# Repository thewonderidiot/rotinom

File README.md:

# rotinom
PCB and FPGA projects for an AGC test connector electrical simulation board, for testing the AGC Monitor.

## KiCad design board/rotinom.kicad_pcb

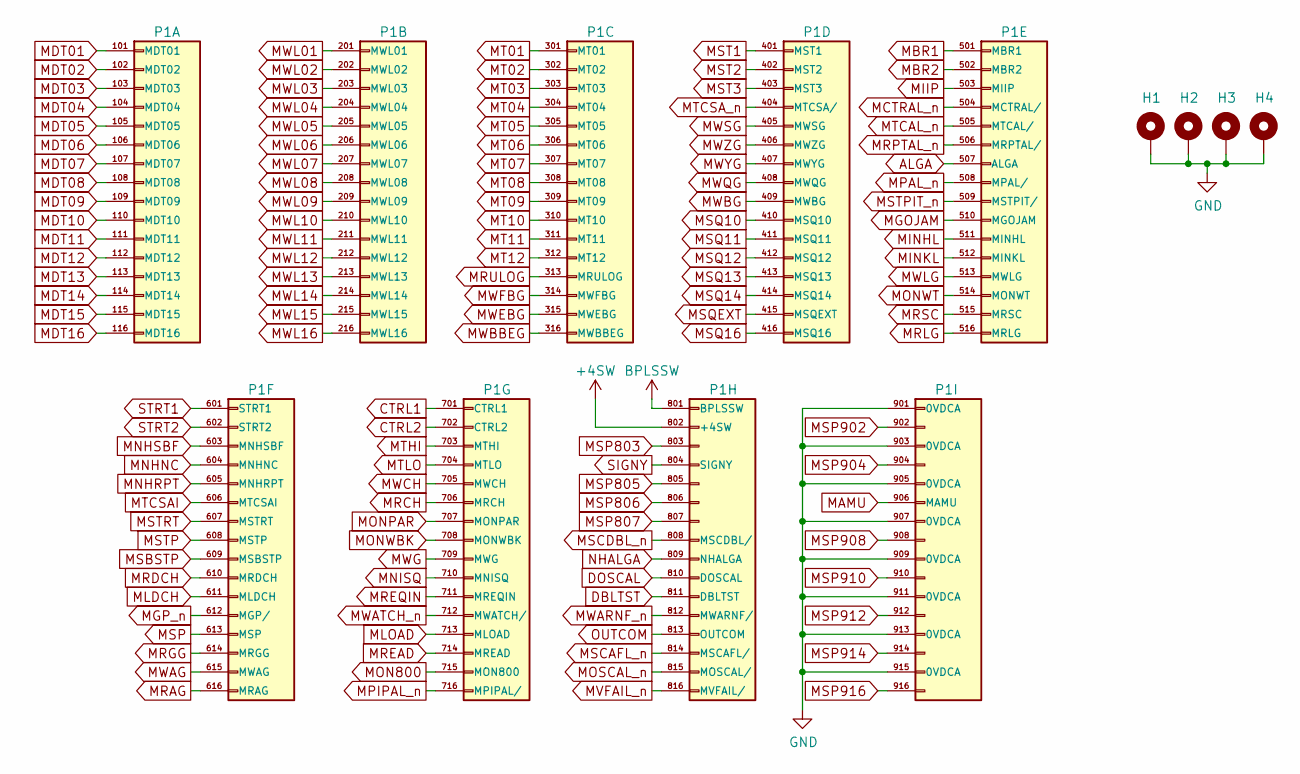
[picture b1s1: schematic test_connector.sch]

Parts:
H1, H2, H3, H4: MountingHole_Pad; MountingHole_ANSI_4
P1: test_connector

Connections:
+4SW: P1.802 (+4SW); also elsewhere on the board
ALGA: P1.507 (ALGA); also elsewhere on the board
BPLSSW: P1.801 (BPLSSW); also elsewhere on the board
CTRL1: P1.701 (CTRL1); also elsewhere on the board
CTRL2: P1.702 (CTRL2); also elsewhere on the board
DBLTST: P1.811 (DBLTST); also elsewhere on the board
DOSCAL: P1.810 (DOSCAL); also elsewhere on the board
GND: H1.1, H2.1, H3.1, H4.1, P1.901 (0VDCA), P1.903 (0VDCA), P1.905 (0VDCA), P1.907 (0VDCA), P1.909 (0VDCA), P1.911 (0VDCA), P1.913 (0VDCA), P1.915 (0VDCA); also elsewhere on the board
MAMU: P1.906 (MAMU); also elsewhere on the board
MBR1: P1.501 (MBR1); also elsewhere on the board
MBR2: P1.502 (MBR2); also elsewhere on the board
MCTRAL_n: P1.504 (MCTRAL/); also elsewhere on the board
MDT01: P1.101 (MDT01); also elsewhere on the board
MDT02: P1.102 (MDT02); also elsewhere on the board
MDT03: P1.103 (MDT03); also elsewhere on the board
MDT04: P1.104 (MDT04); also elsewhere on the board
MDT05: P1.105 (MDT05); also elsewhere on the board
MDT06: P1.106 (MDT06); also elsewhere on the board
MDT07: P1.107 (MDT07); also elsewhere on the board
MDT08: P1.108 (MDT08); also elsewhere on the board
MDT09: P1.109 (MDT09); also elsewhere on the board
MDT10: P1.110 (MDT10); also elsewhere on the board
MDT11: P1.111 (MDT11); also elsewhere on the board
MDT12: P1.112 (MDT12); also elsewhere on the board
MDT13: P1.113 (MDT13); also elsewhere on the board
MDT14: P1.114 (MDT14); also elsewhere on the board
MDT15: P1.115 (MDT15); also elsewhere on the board
MDT16: P1.116 (MDT16); also elsewhere on the board
MGOJAM: P1.510 (MGOJAM); also elsewhere on the board
MGP_n: P1.612 (MGP/); also elsewhere on the board
MIIP: P1.503 (MIIP); also elsewhere on the board
MINHL: P1.511 (MINHL); also elsewhere on the board
MINKL: P1.512 (MINKL); also elsewhere on the board
MLDCH: P1.611 (MLDCH); also elsewhere on the board
MLOAD: P1.713 (MLOAD); also elsewhere on the board
MNHNC: P1.604 (MNHNC); also elsewhere on the board
MNHRPT: P1.605 (MNHRPT); also elsewhere on the board
MNHSBF: P1.603 (MNHSBF); also elsewhere on the board
MNISQ: P1.710 (MNISQ); also elsewhere on the board
MON800: P1.715 (MON800); also elsewhere on the board
MONPAR: P1.707 (MONPAR); also elsewhere on the board
MONWBK: P1.708 (MONWBK); also elsewhere on the board
MONWT: P1.514 (MONWT); also elsewhere on the board
MOSCAL_n: P1.815 (MOSCAL/); also elsewhere on the board
MPAL_n: P1.508 (MPAL/); also elsewhere on the board
MPIPAL_n: P1.716 (MPIPAL/); also elsewhere on the board
MRAG: P1.616 (MRAG); also elsewhere on the board
MRCH: P1.706 (MRCH); also elsewhere on the board
MRDCH: P1.610 (MRDCH); also elsewhere on the board
MREAD: P1.714 (MREAD); also elsewhere on the board
MREQIN: P1.711 (MREQIN); also elsewhere on the board
MRGG: P1.614 (MRGG); also elsewhere on the board
MRLG: P1.516 (MRLG); also elsewhere on the board
MRPTAL_n: P1.506 (MRPTAL/); also elsewhere on the board
MRSC: P1.515 (MRSC); also elsewhere on the board
MRULOG: P1.313 (MRULOG); also elsewhere on the board
MSBSTP: P1.609 (MSBSTP); also elsewhere on the board
MSCAFL_n: P1.814 (MSCAFL/); also elsewhere on the board
MSCDBL_n: P1.808 (MSCDBL/); also elsewhere on the board
MSP: P1.613 (MSP); also elsewhere on the board
MSP803: P1.803; also elsewhere on the board
MSP805: P1.805; also elsewhere on the board
MSP806: P1.806; also elsewhere on the board
MSP807: P1.807; also elsewhere on the board
MSP902: P1.902; also elsewhere on the board
MSP904: P1.904; also elsewhere on the board
MSP908: P1.908; also elsewhere on the board
MSP910: P1.910; also elsewhere on the board
MSP912: P1.912; also elsewhere on the board
MSP914: P1.914; also elsewhere on the board
MSP916: P1.916; also elsewhere on the board
MSQ10: P1.410 (MSQ10); also elsewhere on the board
MSQ11: P1.411 (MSQ11); also elsewhere on the board
MSQ12: P1.412 (MSQ12); also elsewhere on the board
MSQ13: P1.413 (MSQ13); also elsewhere on the board
MSQ14: P1.414 (MSQ14); also elsewhere on the board
MSQ16: P1.416 (MSQ16); also elsewhere on the board
MSQEXT: P1.415 (MSQEXT); also elsewhere on the board
MST1: P1.401 (MST1); also elsewhere on the board
MST2: P1.402 (MST2); also elsewhere on the board
MST3: P1.403 (MST3); also elsewhere on the board
MSTP: P1.608 (MSTP); also elsewhere on the board
MSTPIT_n: P1.509 (MSTPIT/); also elsewhere on the board
MSTRT: P1.607 (MSTRT); also elsewhere on the board
MT01: P1.301 (MT01); also elsewhere on the board
MT02: P1.302 (MT02); also elsewhere on the board
MT03: P1.303 (MT03); also elsewhere on the board
MT04: P1.304 (MT04); also elsewhere on the board
MT05: P1.305 (MT05); also elsewhere on the board
MT06: P1.306 (MT06); also elsewhere on the board
MT07: P1.307 (MT07); also elsewhere on the board
MT08: P1.308 (MT08); also elsewhere on the board
MT09: P1.309 (MT09); also elsewhere on the board
MT10: P1.310 (MT10); also elsewhere on the board
MT11: P1.311 (MT11); also elsewhere on the board
MT12: P1.312 (MT12); also elsewhere on the board
MTCAL_n: P1.505 (MTCAL/); also elsewhere on the board
MTCSAI: P1.606 (MTCSAI); also elsewhere on the board
MTCSA_n: P1.404 (MTCSA/); also elsewhere on the board
MTHI: P1.703 (MTHI); also elsewhere on the board
MTLO: P1.704 (MTLO); also elsewhere on the board
MVFAIL_n: P1.816 (MVFAIL/); also elsewhere on the board
MWAG: P1.615 (MWAG); also elsewhere on the board
MWARNF_n: P1.812 (MWARNF/); also elsewhere on the board
MWATCH_n: P1.712 (MWATCH/); also elsewhere on the board
MWBBEG: P1.316 (MWBBEG); also elsewhere on the board
MWBG: P1.409 (MWBG); also elsewhere on the board
MWCH: P1.705 (MWCH); also elsewhere on the board
MWEBG: P1.315 (MWEBG); also elsewhere on the board
MWFBG: P1.314 (MWFBG); also elsewhere on the board
MWG: P1.709 (MWG); also elsewhere on the board
MWL01: P1.201 (MWL01); also elsewhere on the board
MWL02: P1.202 (MWL02); also elsewhere on the board
MWL03: P1.203 (MWL03); also elsewhere on the board
MWL04: P1.204 (MWL04); also elsewhere on the board
MWL05: P1.205 (MWL05); also elsewhere on the board
MWL06: P1.206 (MWL06); also elsewhere on the board
MWL07: P1.207 (MWL07); also elsewhere on the board
MWL08: P1.208 (MWL08); also elsewhere on the board
MWL09: P1.209 (MWL09); also elsewhere on the board
MWL10: P1.210 (MWL10); also elsewhere on the board
MWL11: P1.211 (MWL11); also elsewhere on the board
MWL12: P1.212 (MWL12); also elsewhere on the board
MWL13: P1.213 (MWL13); also elsewhere on the board
MWL14: P1.214 (MWL14); also elsewhere on the board
MWL15: P1.215 (MWL15); also elsewhere on the board
MWL16: P1.216 (MWL16); also elsewhere on the board
MWLG: P1.513 (MWLG); also elsewhere on the board
MWQG: P1.408 (MWQG); also elsewhere on the board
MWSG: P1.405 (MWSG); also elsewhere on the board
MWYG: P1.407 (MWYG); also elsewhere on the board
MWZG: P1.406 (MWZG); also elsewhere on the board
NHALGA: P1.809 (NHALGA); also elsewhere on the board
OUTCOM: P1.813 (OUTCOM); also elsewhere on the board
SIGNY: P1.804 (SIGNY); also elsewhere on the board
STRT1: P1.601 (STRT1); also elsewhere on the board
STRT2: P1.602 (STRT2); also elsewhere on the board

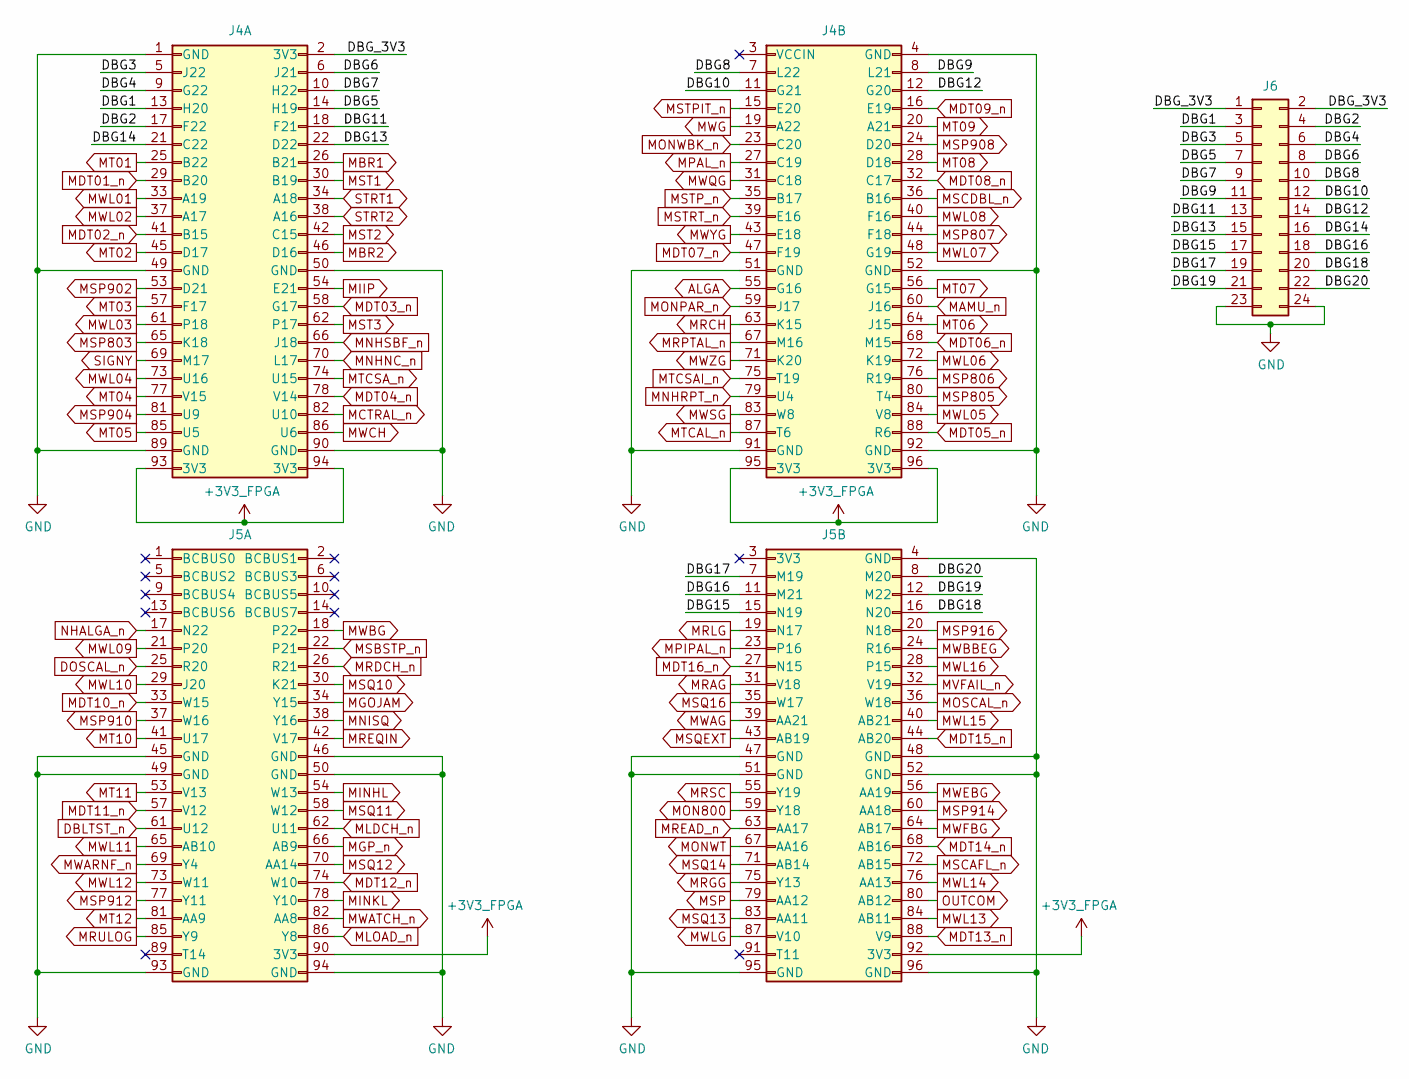
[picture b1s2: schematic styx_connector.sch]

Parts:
J4: Styx_P4; PinHeader_4x24_P2.54mm_Vertical
J5: Styx_P5; PinHeader_4x24_P2.54mm_Vertical
J6: Conn_02x12_Odd_Even; PinSocket_2x12_P2.54mm_Vertical

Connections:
+3V3_FPGA: J4.93 (3V3), J4.94 (3V3), J4.95 (3V3), J4.96 (3V3), J5.90 (3V3), J5.92 (3V3); also elsewhere on the board
/StyxConnector/DBG15: J5.15 (N19), J6.17
/StyxConnector/DBG16: J5.11 (M21), J6.18
/StyxConnector/DBG17: J5.7 (M19), J6.19
/StyxConnector/DBG18: J5.16 (N20), J6.20
/StyxConnector/DBG19: J5.12 (M22), J6.21
/StyxConnector/DBG20: J5.8 (M20), J6.22
/StyxConnector/DBG_3V3: J4.2 (3V3), J6.1, J6.2
ALGA: J4.55 (G16); also elsewhere on the board
DBLTST_n: J5.61 (U12); also elsewhere on the board
DOSCAL_n: J5.25 (R20); also elsewhere on the board
GND: J4.1 (GND), J4.4 (GND), J4.49 (GND), J4.50 (GND), J4.51 (GND), J4.52 (GND), J4.89 (GND), J4.90 (GND), J4.91 (GND), J4.92 (GND), J5.4 (GND), J5.45 (GND), J5.46 (GND), J5.47 (GND), J5.48 (GND), J5.49 (GND), J5.50 (GND), J5.51 (GND), J5.52 (GND), J5.93 (GND), J5.94 (GND), J5.95 (GND), J5.96 (GND), J6.23, J6.24; also elsewhere on the board
MAMU_n: J4.60 (J16); also elsewhere on the board
MBR1: J4.26 (B21); also elsewhere on the board
MBR2: J4.46 (D16); also elsewhere on the board
MCTRAL_n: J4.82 (U10); also elsewhere on the board
MDT01_n: J4.29 (B20); also elsewhere on the board
MDT02_n: J4.41 (B15); also elsewhere on the board
MDT03_n: J4.58 (G17); also elsewhere on the board
MDT04_n: J4.78 (V14); also elsewhere on the board
MDT05_n: J4.88 (R6); also elsewhere on the board
MDT06_n: J4.68 (M15); also elsewhere on the board
MDT07_n: J4.47 (F19); also elsewhere on the board
MDT08_n: J4.32 (C17); also elsewhere on the board
MDT09_n: J4.16 (E19); also elsewhere on the board
MDT10_n: J5.33 (W15); also elsewhere on the board
MDT11_n: J5.57 (V12); also elsewhere on the board
MDT12_n: J5.74 (W10); also elsewhere on the board
MDT13_n: J5.88 (V9); also elsewhere on the board
MDT14_n: J5.68 (AB16); also elsewhere on the board
MDT15_n: J5.44 (AB20); also elsewhere on the board
MDT16_n: J5.27 (N15); also elsewhere on the board
MGOJAM: J5.34 (Y15); also elsewhere on the board
MGP_n: J5.66 (AB9); also elsewhere on the board
MIIP: J4.54 (E21); also elsewhere on the board
MINHL: J5.54 (W13); also elsewhere on the board
MINKL: J5.78 (Y10); also elsewhere on the board
MLDCH_n: J5.62 (U11); also elsewhere on the board
MLOAD_n: J5.86 (Y8); also elsewhere on the board
MNHNC_n: J4.70 (L17); also elsewhere on the board
MNHRPT_n: J4.79 (U4); also elsewhere on the board
MNHSBF_n: J4.66 (J18); also elsewhere on the board
MNISQ: J5.38 (Y16); also elsewhere on the board
MON800: J5.59 (Y18); also elsewhere on the board
MONPAR_n: J4.59 (J17); also elsewhere on the board
MONWBK_n: J4.23 (C20); also elsewhere on the board
MONWT: J5.67 (AA16); also elsewhere on the board
MOSCAL_n: J5.36 (W18); also elsewhere on the board
MPAL_n: J4.27 (C19); also elsewhere on the board
MPIPAL_n: J5.23 (P16); also elsewhere on the board
MRAG: J5.31 (V18); also elsewhere on the board
MRCH: J4.63 (K15); also elsewhere on the board
MRDCH_n: J5.26 (R21); also elsewhere on the board
MREAD_n: J5.63 (AA17); also elsewhere on the board
MREQIN: J5.42 (V17); also elsewhere on the board
MRGG: J5.75 (Y13); also elsewhere on the board
MRLG: J5.19 (N17); also elsewhere on the board
MRPTAL_n: J4.67 (M16); also elsewhere on the board
MRSC: J5.55 (Y19); also elsewhere on the board
MRULOG: J5.85 (Y9); also elsewhere on the board
MSBSTP_n: J5.22 (P21); also elsewhere on the board
MSCAFL_n: J5.72 (AB15); also elsewhere on the board
MSCDBL_n: J4.36 (B16); also elsewhere on the board
MSP: J5.79 (AA12); also elsewhere on the board
MSP803: J4.65 (K18); also elsewhere on the board
MSP805: J4.80 (T4); also elsewhere on the board
MSP806: J4.76 (R19); also elsewhere on the board
MSP807: J4.44 (F18); also elsewhere on the board
MSP902: J4.53 (D21); also elsewhere on the board
MSP904: J4.81 (U9); also elsewhere on the board
MSP908: J4.24 (D20); also elsewhere on the board
MSP910: J5.37 (W16); also elsewhere on the board
MSP912: J5.77 (Y11); also elsewhere on the board
MSP914: J5.60 (AA18); also elsewhere on the board
MSP916: J5.20 (N18); also elsewhere on the board
MSQ10: J5.30 (K21); also elsewhere on the board
MSQ11: J5.58 (W12); also elsewhere on the board
MSQ12: J5.70 (AA14); also elsewhere on the board
MSQ13: J5.83 (AA11); also elsewhere on the board
MSQ14: J5.71 (AB14); also elsewhere on the board
MSQ16: J5.35 (W17); also elsewhere on the board
MSQEXT: J5.43 (AB19); also elsewhere on the board
MST1: J4.30 (B19); also elsewhere on the board
MST2: J4.42 (C15); also elsewhere on the board
MST3: J4.62 (P17); also elsewhere on the board
MSTPIT_n: J4.15 (E20); also elsewhere on the board
MSTP_n: J4.35 (B17); also elsewhere on the board
MSTRT_n: J4.39 (E16); also elsewhere on the board
MT01: J4.25 (B22); also elsewhere on the board
MT02: J4.45 (D17); also elsewhere on the board
MT03: J4.57 (F17); also elsewhere on the board
MT04: J4.77 (V15); also elsewhere on the board
MT05: J4.85 (U5); also elsewhere on the board
MT06: J4.64 (J15); also elsewhere on the board
MT07: J4.56 (G15); also elsewhere on the board
MT08: J4.28 (D18); also elsewhere on the board
MT09: J4.20 (A21); also elsewhere on the board
MT10: J5.41 (U17); also elsewhere on the board
MT11: J5.53 (V13); also elsewhere on the board
MT12: J5.81 (AA9); also elsewhere on the board
MTCAL_n: J4.87 (T6); also elsewhere on the board
MTCSAI_n: J4.75 (T19); also elsewhere on the board
MTCSA_n: J4.74 (U15); also elsewhere on the board
MVFAIL_n: J5.32 (V19); also elsewhere on the board
MWAG: J5.39 (AA21); also elsewhere on the board
MWARNF_n: J5.69 (Y4); also elsewhere on the board
MWATCH_n: J5.82 (AA8); also elsewhere on the board
MWBBEG: J5.24 (R16); also elsewhere on the board
MWBG: J5.18 (P22); also elsewhere on the board
MWCH: J4.86 (U6); also elsewhere on the board
MWEBG: J5.56 (AA19); also elsewhere on the board
MWFBG: J5.64 (AB17); also elsewhere on the board
MWG: J4.19 (A22); also elsewhere on the board
MWL01: J4.33 (A19); also elsewhere on the board
MWL02: J4.37 (A17); also elsewhere on the board
MWL03: J4.61 (P18); also elsewhere on the board
MWL04: J4.73 (U16); also elsewhere on the board
MWL05: J4.84 (V8); also elsewhere on the board
MWL06: J4.72 (K19); also elsewhere on the board
MWL07: J4.48 (G19); also elsewhere on the board
MWL08: J4.40 (F16); also elsewhere on the board
MWL09: J5.21 (P20); also elsewhere on the board
MWL10: J5.29 (J20); also elsewhere on the board
MWL11: J5.65 (AB10); also elsewhere on the board
MWL12: J5.73 (W11); also elsewhere on the board
MWL13: J5.84 (AB11); also elsewhere on the board
MWL14: J5.76 (AA13); also elsewhere on the board
MWL15: J5.40 (AB21); also elsewhere on the board
MWL16: J5.28 (P15); also elsewhere on the board
MWLG: J5.87 (V10); also elsewhere on the board
MWQG: J4.31 (C18); also elsewhere on the board
MWSG: J4.83 (W8); also elsewhere on the board
MWYG: J4.43 (E18); also elsewhere on the board
MWZG: J4.71 (K20); also elsewhere on the board
NHALGA_n: J5.17 (N22); also elsewhere on the board
OUTCOM: J5.80 (AB12); also elsewhere on the board
SIGNY: J4.69 (M17); also elsewhere on the board
STRT1: J4.34 (A18); also elsewhere on the board
STRT2: J4.38 (A16); also elsewhere on the board

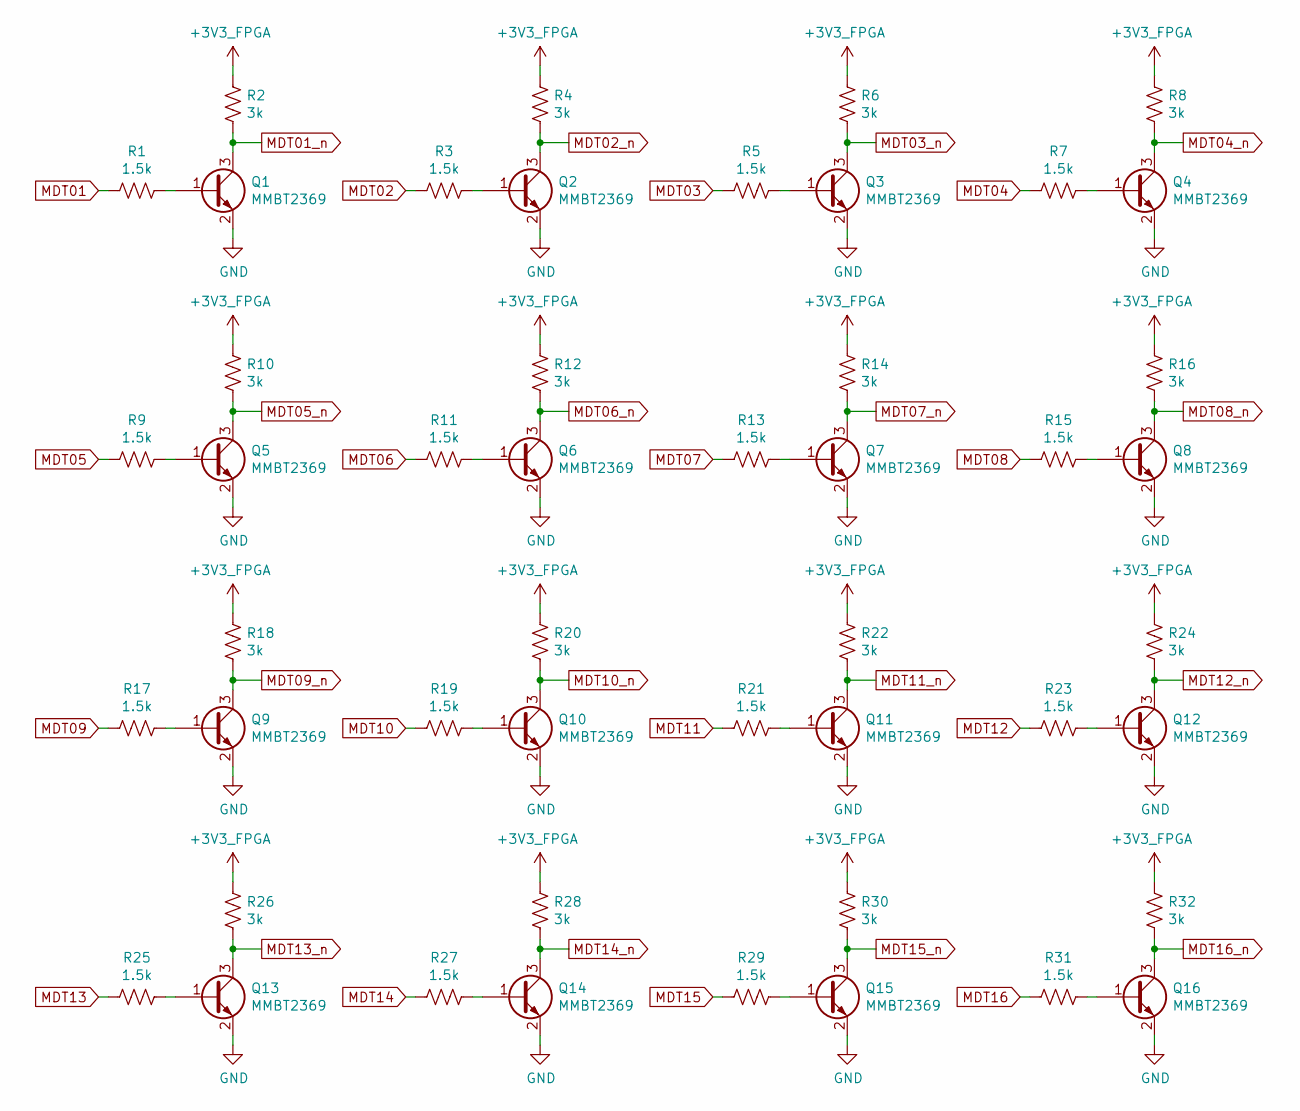
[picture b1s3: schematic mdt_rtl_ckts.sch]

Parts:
Q1, Q2, Q3, Q4, Q5, Q6, Q7, Q8, Q9, Q10, Q11, Q12, Q13, Q14, Q15, Q16: MMBT2369; SOT-23
R1, R3, R5, R7, R9, R11, R13, R15, R17, R19, R21, R23, R25, R27, R29, R31: 1.5k; R_0603_1608Metric
R2, R4, R6, R8, R10, R12, R14, R16, R18, R20, R22, R24, R26, R28, R30, R32: 3k; R_0603_1608Metric

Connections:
+3V3_FPGA: R2.1, R4.1, R6.1, R8.1, R10.1, R12.1, R14.1, R16.1, R18.1, R20.1, R22.1, R24.1, R26.1, R28.1, R30.1, R32.1; also elsewhere on the board
GND: Q1.2 (E), Q2.2 (E), Q3.2 (E), Q4.2 (E), Q5.2 (E), Q6.2 (E), Q7.2 (E), Q8.2 (E), Q9.2 (E), Q10.2 (E), Q11.2 (E), Q12.2 (E), Q13.2 (E), Q14.2 (E), Q15.2 (E), Q16.2 (E); also elsewhere on the board
MDT01: R1.2; also elsewhere on the board
MDT01_n: Q1.3 (C), R2.2; also elsewhere on the board
MDT02: R3.2; also elsewhere on the board
MDT02_n: Q2.3 (C), R4.2; also elsewhere on the board
MDT03: R5.2; also elsewhere on the board
MDT03_n: Q3.3 (C), R6.2; also elsewhere on the board
MDT04: R7.2; also elsewhere on the board
MDT04_n: Q4.3 (C), R8.2; also elsewhere on the board
MDT05: R9.2; also elsewhere on the board
MDT05_n: Q5.3 (C), R10.2; also elsewhere on the board
MDT06: R11.2; also elsewhere on the board
MDT06_n: Q6.3 (C), R12.2; also elsewhere on the board
MDT07: R13.2; also elsewhere on the board
MDT07_n: Q7.3 (C), R14.2; also elsewhere on the board
MDT08: R15.2; also elsewhere on the board
MDT08_n: Q8.3 (C), R16.2; also elsewhere on the board
MDT09: R17.2; also elsewhere on the board
MDT09_n: Q9.3 (C), R18.2; also elsewhere on the board
MDT10: R19.2; also elsewhere on the board
MDT10_n: Q10.3 (C), R20.2; also elsewhere on the board
MDT11: R21.2; also elsewhere on the board
MDT11_n: Q11.3 (C), R22.2; also elsewhere on the board
MDT12: R23.2; also elsewhere on the board
MDT12_n: Q12.3 (C), R24.2; also elsewhere on the board
MDT13: R25.2; also elsewhere on the board
MDT13_n: Q13.3 (C), R26.2; also elsewhere on the board
MDT14: R27.2; also elsewhere on the board
MDT14_n: Q14.3 (C), R28.2; also elsewhere on the board
MDT15: R29.2; also elsewhere on the board
MDT15_n: Q15.3 (C), R30.2; also elsewhere on the board
MDT16: R31.2; also elsewhere on the board
MDT16_n: Q16.3 (C), R32.2; also elsewhere on the board
unnamed: Q1.1 (B), R1.1
unnamed: Q2.1 (B), R3.1
unnamed: Q3.1 (B), R5.1
unnamed: Q4.1 (B), R7.1
unnamed: Q5.1 (B), R9.1
unnamed: Q6.1 (B), R11.1
unnamed: Q7.1 (B), R13.1
unnamed: Q8.1 (B), R15.1
unnamed: Q9.1 (B), R17.1
unnamed: Q10.1 (B), R19.1
unnamed: Q11.1 (B), R21.1
unnamed: Q12.1 (B), R23.1
unnamed: Q13.1 (B), R25.1
unnamed: Q14.1 (B), R27.1
unnamed: Q15.1 (B), R29.1
unnamed: Q16.1 (B), R31.1

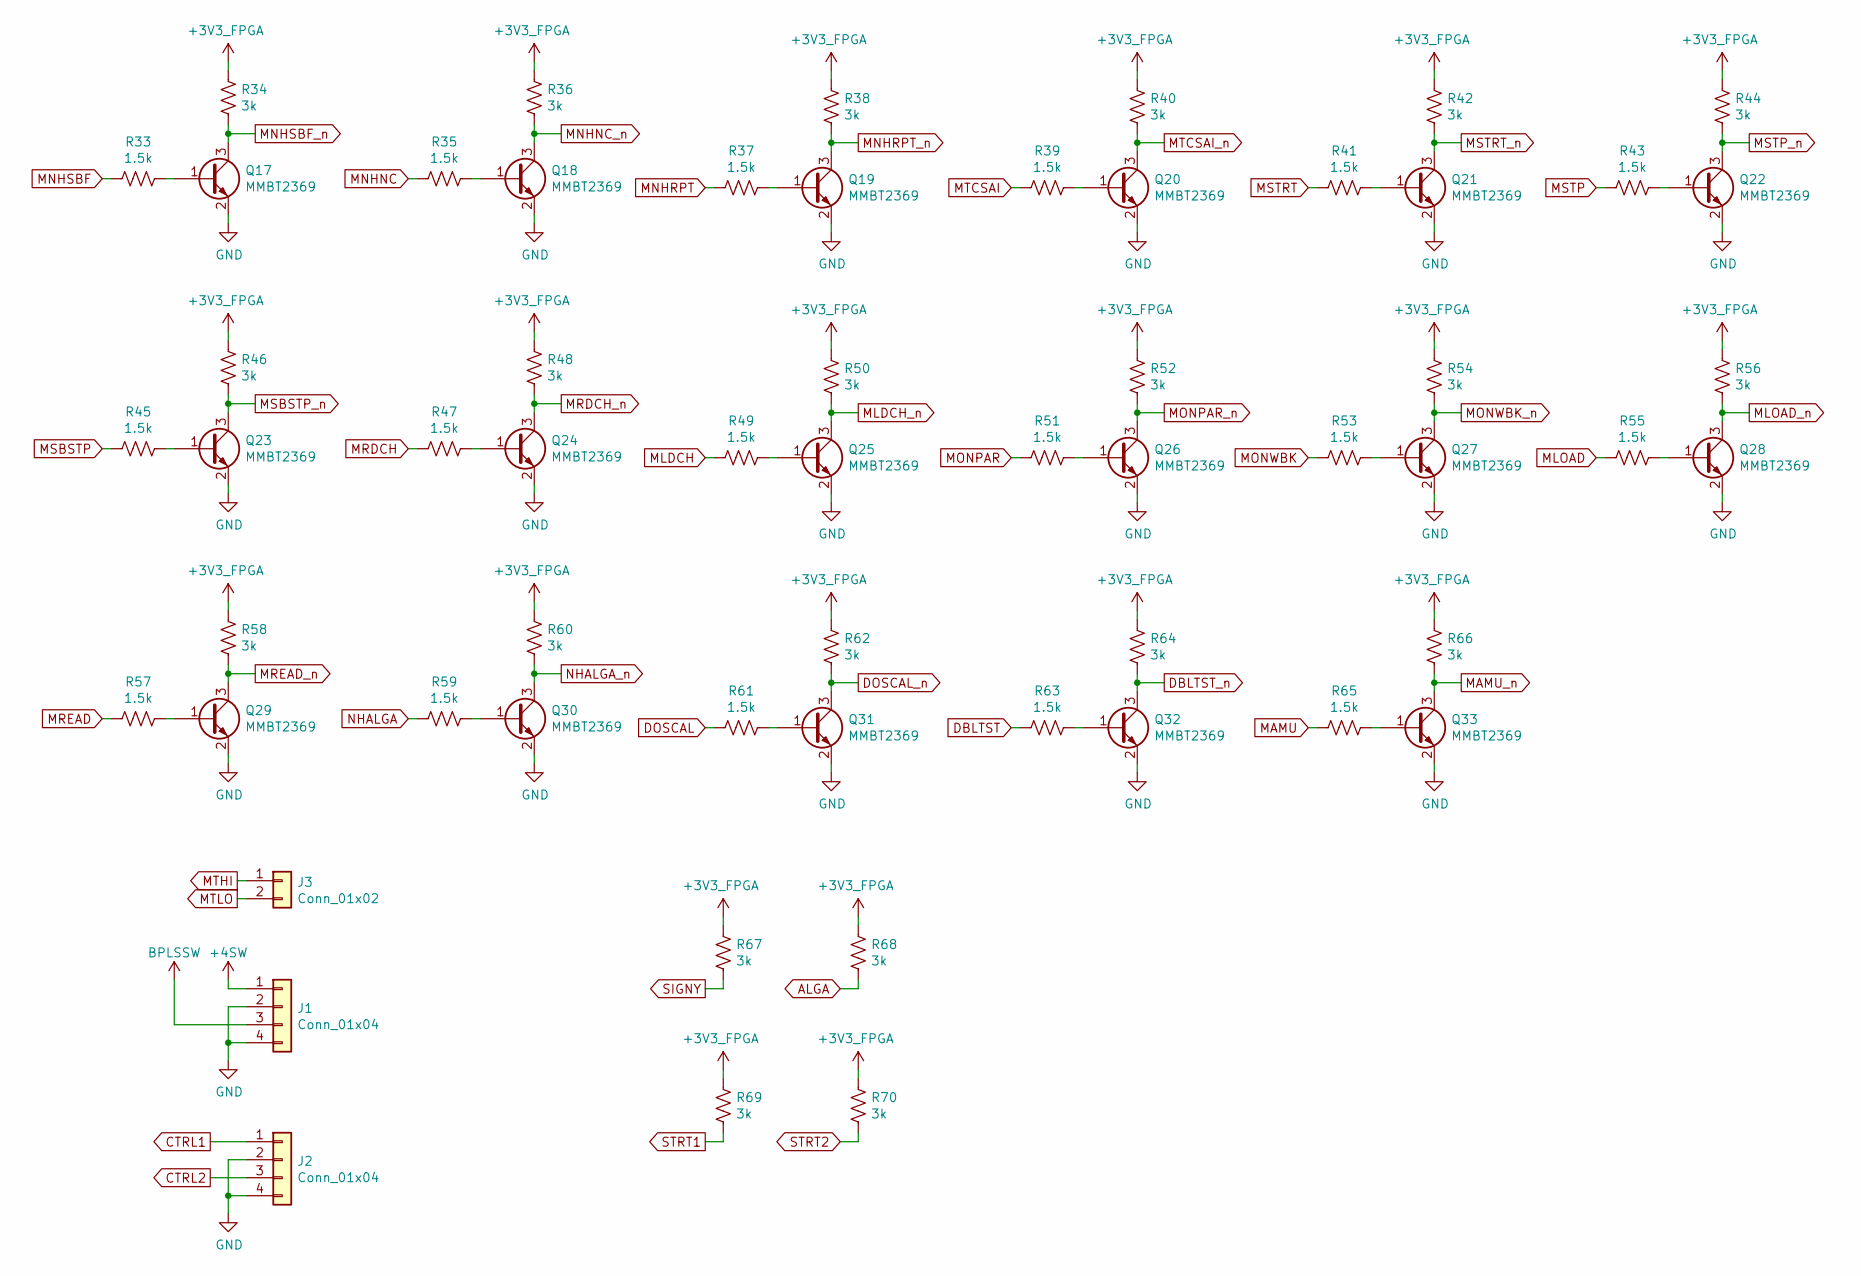
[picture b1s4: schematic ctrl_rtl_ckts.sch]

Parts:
J1, J2: Conn_01x04; PinSocket_1x04_P2.54mm_Vertical
J3: Conn_01x02; PinSocket_1x02_P2.54mm_Vertical
Q17, Q18, Q19, Q20, Q21, Q22, Q23, Q24, Q25, Q26, Q27, Q28, Q29, Q30, Q31, Q32, Q33: MMBT2369; SOT-23
R33, R35, R37, R39, R41, R43, R45, R47, R49, R51, R53, R55, R57, R59, R61, R63, R65: 1.5k; R_0603_1608Metric
R34, R36, R38, R40, R42, R44, R46, R48, R50, R52, R54, R56, R58, R60, R62, R64, R66, R67, R68, R69, R70: 3k; R_0603_1608Metric

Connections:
+3V3_FPGA: R34.1, R36.1, R38.1, R40.1, R42.1, R44.1, R46.1, R48.1, R50.1, R52.1, R54.1, R56.1, R58.1, R60.1, R62.1, R64.1, R66.1, R67.1, R68.1, R69.1, R70.1; also elsewhere on the board
+4SW: J1.1; also elsewhere on the board
ALGA: R68.2; also elsewhere on the board
BPLSSW: J1.3; also elsewhere on the board
CTRL1: J2.1; also elsewhere on the board
CTRL2: J2.3; also elsewhere on the board
DBLTST: R63.2; also elsewhere on the board
DBLTST_n: Q32.3 (C), R64.2; also elsewhere on the board
DOSCAL: R61.2; also elsewhere on the board
DOSCAL_n: Q31.3 (C), R62.2; also elsewhere on the board
GND: J1.2, J1.4, J2.2, J2.4, Q17.2 (E), Q18.2 (E), Q19.2 (E), Q20.2 (E), Q21.2 (E), Q22.2 (E), Q23.2 (E), Q24.2 (E), Q25.2 (E), Q26.2 (E), Q27.2 (E), Q28.2 (E), Q29.2 (E), Q30.2 (E), Q31.2 (E), Q32.2 (E), Q33.2 (E); also elsewhere on the board
MAMU: R65.2; also elsewhere on the board
MAMU_n: Q33.3 (C), R66.2; also elsewhere on the board
MLDCH: R49.2; also elsewhere on the board
MLDCH_n: Q25.3 (C), R50.2; also elsewhere on the board
MLOAD: R55.2; also elsewhere on the board
MLOAD_n: Q28.3 (C), R56.2; also elsewhere on the board
MNHNC: R35.2; also elsewhere on the board
MNHNC_n: Q18.3 (C), R36.2; also elsewhere on the board
MNHRPT: R37.2; also elsewhere on the board
MNHRPT_n: Q19.3 (C), R38.2; also elsewhere on the board
MNHSBF: R33.2; also elsewhere on the board
MNHSBF_n: Q17.3 (C), R34.2; also elsewhere on the board
MONPAR: R51.2; also elsewhere on the board
MONPAR_n: Q26.3 (C), R52.2; also elsewhere on the board
MONWBK: R53.2; also elsewhere on the board
MONWBK_n: Q27.3 (C), R54.2; also elsewhere on the board
MRDCH: R47.2; also elsewhere on the board
MRDCH_n: Q24.3 (C), R48.2; also elsewhere on the board
MREAD: R57.2; also elsewhere on the board
MREAD_n: Q29.3 (C), R58.2; also elsewhere on the board
MSBSTP: R45.2; also elsewhere on the board
MSBSTP_n: Q23.3 (C), R46.2; also elsewhere on the board
MSTP: R43.2; also elsewhere on the board
MSTP_n: Q22.3 (C), R44.2; also elsewhere on the board
MSTRT: R41.2; also elsewhere on the board
MSTRT_n: Q21.3 (C), R42.2; also elsewhere on the board
MTCSAI: R39.2; also elsewhere on the board
MTCSAI_n: Q20.3 (C), R40.2; also elsewhere on the board
MTHI: J3.1; also elsewhere on the board
MTLO: J3.2; also elsewhere on the board
NHALGA: R59.2; also elsewhere on the board
NHALGA_n: Q30.3 (C), R60.2; also elsewhere on the board
unnamed: Q17.1 (B), R33.1
unnamed: Q18.1 (B), R35.1
unnamed: Q19.1 (B), R37.1
unnamed: Q20.1 (B), R39.1
unnamed: Q21.1 (B), R41.1
unnamed: Q22.1 (B), R43.1
unnamed: Q23.1 (B), R45.1
unnamed: Q24.1 (B), R47.1
unnamed: Q25.1 (B), R49.1
unnamed: Q26.1 (B), R51.1
unnamed: Q27.1 (B), R53.1
unnamed: Q28.1 (B), R55.1
unnamed: Q29.1 (B), R57.1
unnamed: Q30.1 (B), R59.1
unnamed: Q31.1 (B), R61.1
unnamed: Q32.1 (B), R63.1
unnamed: Q33.1 (B), R65.1
SIGNY: R67.2; also elsewhere on the board
STRT1: R69.2; also elsewhere on the board
STRT2: R70.2; also elsewhere on the board

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
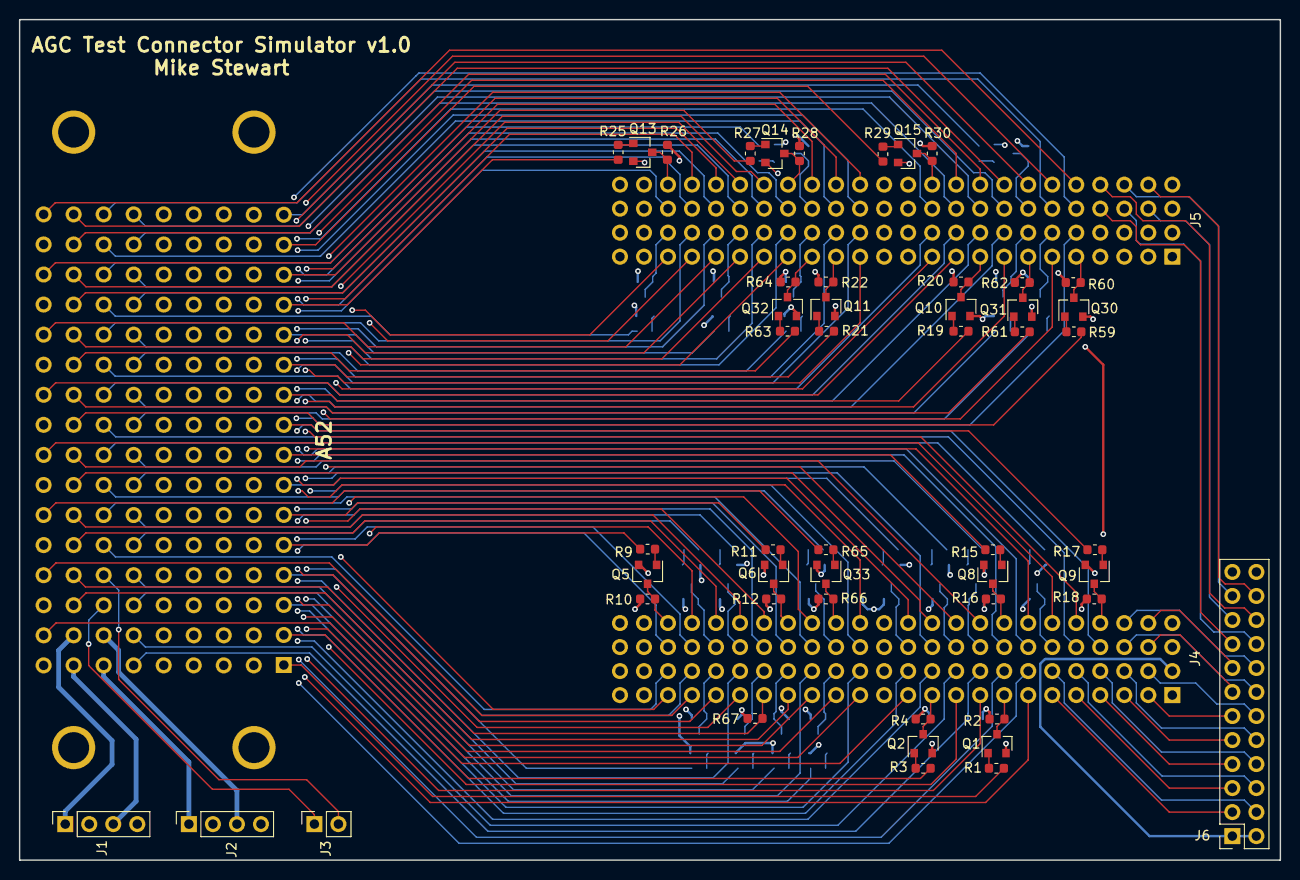
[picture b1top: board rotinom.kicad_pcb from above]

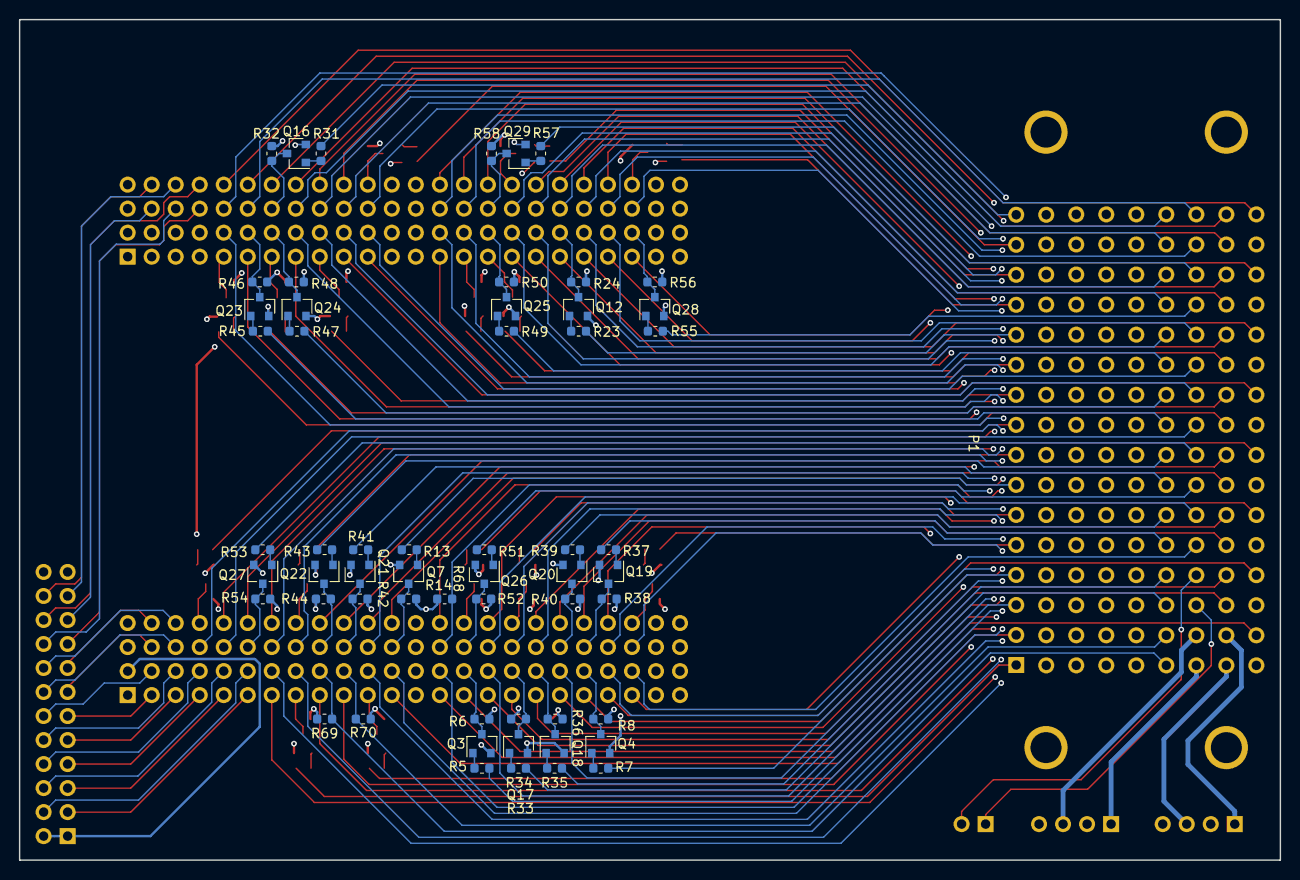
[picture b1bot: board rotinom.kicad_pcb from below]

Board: 4 copper layers, 133.3 x 88.9 mm, 114 parts (59 on the bottom side), 225 nets.

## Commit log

2019-03-28 Added simple README
2019-03-28 Initial schematicery
2019-04-01 Board: 5/8 of the data lanes routed
2019-04-03 Board: Finished routing AGC signals; still need to route 3v3 and ground to RTL circuits
2019-04-04 Board: Basic layout done, but need to make the board longer to avoid mechanical conflict with the monitor
2019-04-04 Board: finished routing of extended board
2019-04-05 Board: minor changes made during gerber export
2019-04-05 Added an FPGA project and ROM files for available ropes
2019-04-20 Board: Updated to use corrected Styx symbol
2019-04-22 FPGA: corrected pin and general project updates
2020-03-18 State of the repository for the July 2019 demos
